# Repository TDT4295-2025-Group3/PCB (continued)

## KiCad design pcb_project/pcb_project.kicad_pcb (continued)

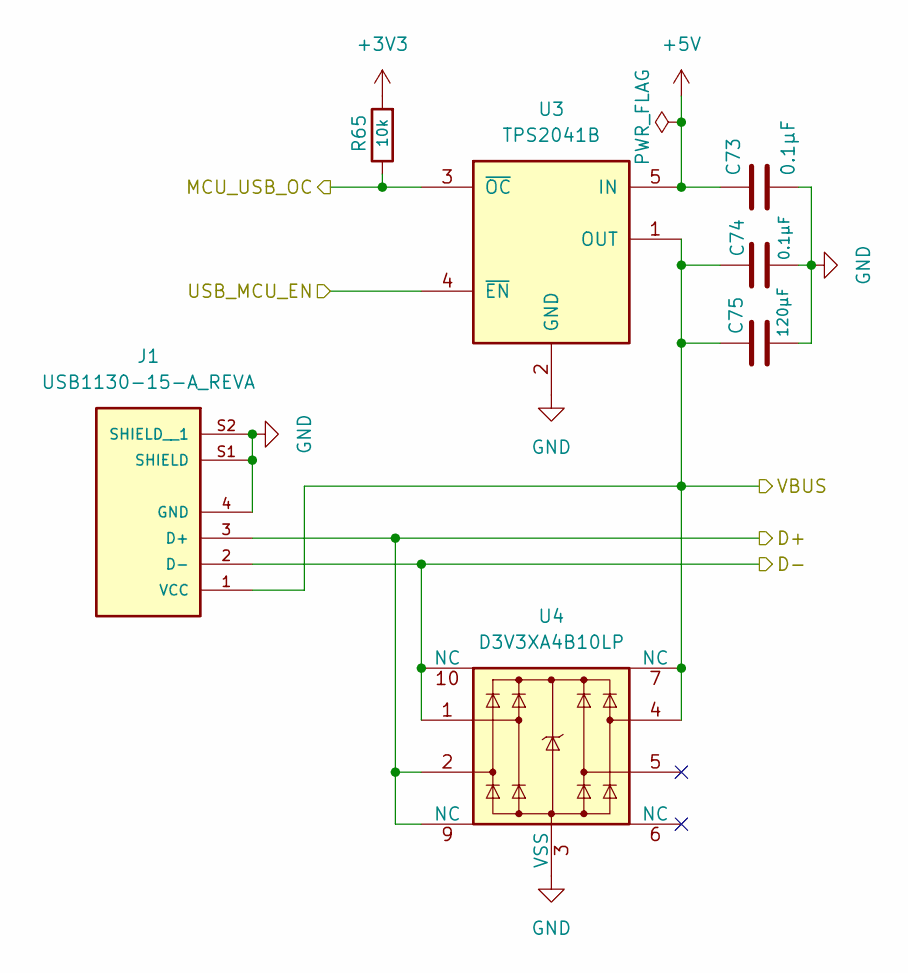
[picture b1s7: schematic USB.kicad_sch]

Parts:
C73: 0.1μF; C_0603_1608Metric_Pad1.08x0.95mm_HandSolder
C74: 0.1µF; C_0603_1608Metric_Pad1.08x0.95mm_HandSolder
C75: 120µF; CP_Elec_6.3x7.7
J1: USB1130-15-A_REVA; GCT_USB1130-15-A_REVA; PARTREV A
R65: 10k; R_0805_2012Metric_Pad1.20x1.40mm_HandSolder
U3: TPS2041B; SOT-23-5
U4: D3V3XA4B10LP; Diodes_UDFN-10_1.0x2.5mm_P0.5mm

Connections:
+3V3: R65.2; also elsewhere on the board
+5V: C73.1, U3.5 (IN); also elsewhere on the board
/MCU/OTG_HS_D+: J1.3 (D+), U4.2, U4.9 (NC); also elsewhere on the board
/MCU/OTG_HS_D-: J1.2 (D-), U4.1, U4.10 (NC); also elsewhere on the board
/MCU/PA9_OTG_HS_VBUS: C74.2, C75.2, J1.1 (VCC), U3.1 (OUT), U4.4, U4.7 (NC); also elsewhere on the board
/MCU/PB0_LPGPIO1_P9: R65.1, U3.3 (~OC); also elsewhere on the board
/MCU/PB1_LPGPIO1_P3: U3.4 (~EN); also elsewhere on the board
GND: C73.2, C74.1, C75.1, J1.4 (GND), J1.S1 (SHIELD), J1.S2 (SHIELD__1), U3.2 (GND), U4.3 (VSS), U4.8 (VSS); also elsewhere on the board

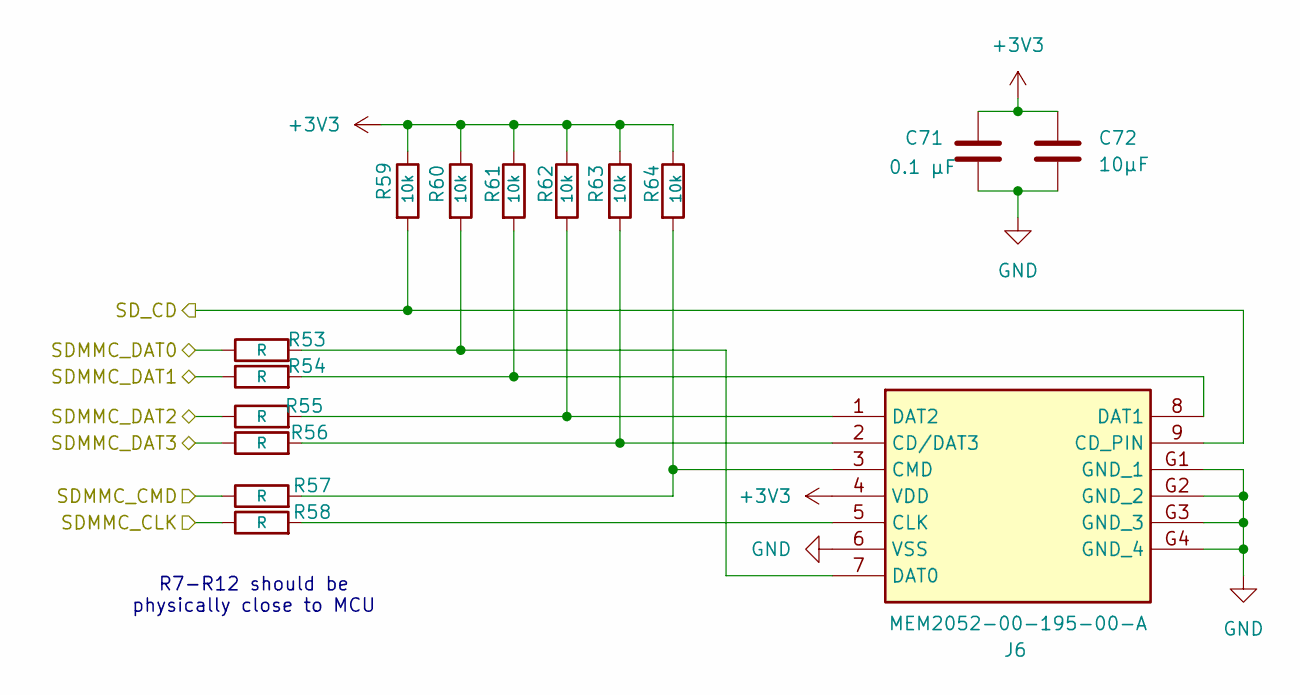
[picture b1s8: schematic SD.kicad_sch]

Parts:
C71: 0.1 µF; C_0603_1608Metric_Pad1.08x0.95mm_HandSolder
C72: 10µF; C_1206_3216Metric_Pad1.33x1.80mm_HandSolder
J6: MEM2052-00-195-00-A; MEM20520019500A; Mouser Part Number 640-MEM20520019500A
R53, R54, R55, R56, R57, R58: R; R_0805_2012Metric_Pad1.20x1.40mm_HandSolder
R59, R60, R61, R62, R63, R64: 10k; R_0805_2012Metric_Pad1.20x1.40mm_HandSolder

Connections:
+3V3: C71.1, C72.1, J6.4 (VDD), R59.1, R60.1, R61.1, R62.1, R63.1, R64.1; also elsewhere on the board
/MCU/PB4_LPGPIO1_P12: J6.9 (CD_PIN), R59.2; also elsewhere on the board
/MCU/PC8_SDMMC1_D0: R53.1; also elsewhere on the board
/MCU/PC9_SDMMC1_D1: R54.1; also elsewhere on the board
/MCU/PC10_SDMMC1_D2: R55.1; also elsewhere on the board
/MCU/PC11_SDMMC1_D3: R56.1; also elsewhere on the board
/MCU/PC12_SDMMC1_CK: R58.1; also elsewhere on the board
/MCU/PD2_SDMMC1_CMD: R57.1; also elsewhere on the board
GND: C71.2, C72.2, J6.6 (VSS), J6.G1 (GND_1), J6.G2 (GND_2), J6.G3 (GND_3), J6.G4 (GND_4); also elsewhere on the board
unnamed: J6.2 (CD/DAT3), R56.2, R63.2
unnamed: J6.5 (CLK), R58.2
unnamed: J6.3 (CMD), R57.2, R64.2
unnamed: J6.7 (DAT0), R53.2, R60.2
unnamed: J6.8 (DAT1), R54.2, R61.2
unnamed: J6.1 (DAT2), R55.2, R62.2

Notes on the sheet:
R7-R12 should be physically close to MCU

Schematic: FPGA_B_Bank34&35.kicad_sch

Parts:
C86: 47µF; C_1210_3225Metric_Pad1.33x2.70mm_HandSolder
C88: 1µF; C_0805_2012Metric_Pad1.18x1.45mm_HandSolder
C89: 0.01µF; C_0603_1608Metric_Pad1.08x0.95mm_HandSolder
C90, C91: 4.7µF; C_0603_1608Metric_Pad1.08x0.95mm_HandSolder
C92, C93, C94, C95: 0.47µF; C_0603_1608Metric_Pad1.08x0.95mm_HandSolder
J8: Conn_01x06_Pin; PinHeader_1x06_P2.54mm_Vertical
R66: 22k; R_0805_2012Metric_Pad1.20x1.40mm_HandSolder
R85, R86: 47; R_0805_2012Metric_Pad1.20x1.40mm_HandSolder
U1: XC7A100T-FTG256; Xilinx_FTG256
Y2: XLH736025.175000I; XLH730003580000I; Mouser Part Number 972-LH736025.175000I

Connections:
+3V3: C86.1, C88.1, C89.1, C90.1, C91.1, C92.1, C93.1, C94.1, C95.1, R66.1, U1.A6 (VCCO_35), U1.B3 (VCCO_35), U1.D7 (VCCO_35), U1.E4 (VCCO_35), U1.F1 (VCCO_35), U1.J2 (VCCO_35), Y2.1 (E/D_/_NC); also elsewhere on the board
/FPGA/B_Bank34&35/GPIO1: J8.1, U1.A7 (IO_L1N_T0_AD4N_35)
/FPGA/B_Bank34&35/GPIO2: J8.2, U1.B7 (IO_L1P_T0_AD4P_35)
/FPGA/B_Bank34&35/GPIO3: J8.3, U1.B6 (IO_L2P_T0_AD12P_35)
/FPGA/B_Bank34&35/GPIO4: J8.4, U1.B5 (IO_L2N_T0_AD12N_35)
/FPGA/B_Bank34&35/GPIO5: J8.5, U1.C7 (IO_L5P_T0_AD13P_35)
/FPGA/B_Bank34&35/GPIO6: J8.6, U1.C6 (IO_L5N_T0_AD13N_35)
/FPGA/HSYNC: R85.2; also elsewhere on the board
/FPGA/OSPI 0: U1.A2 (IO_L8N_T1_AD14N_35); also elsewhere on the board
/FPGA/OSPI 1: U1.A3 (IO_L4N_T0_35); also elsewhere on the board
/FPGA/OSPI 2: U1.A4 (IO_L3N_T0_DQS_AD5N_35); also elsewhere on the board
/FPGA/OSPI 3: U1.A5 (IO_L3P_T0_DQS_AD5P_35); also elsewhere on the board
/FPGA/OSPI 4: U1.E2 (IO_L10P_T1_AD15P_35); also elsewhere on the board
/FPGA/OSPI 5: U1.D1 (IO_L10N_T1_AD15N_35); also elsewhere on the board
/FPGA/OSPI 6: U1.C2 (IO_L7N_T1_AD6N_35); also elsewhere on the board
/FPGA/OSPI 7: U1.C1 (IO_L9P_T1_DQS_AD7P_35); also elsewhere on the board
/FPGA/OSPI CLK: U1.F5 (IO_L13P_T2_MRCC_35); also elsewhere on the board
/FPGA/OSPI CS: R66.2, U1.B2 (IO_L8P_T1_AD14P_35); also elsewhere on the board
/FPGA/VSYNC: R86.2; also elsewhere on the board
/VGA/B0: U1.E1 (IO_L15N_T2_DQS_35); also elsewhere on the board
/VGA/B1: U1.F3 (IO_L14N_T2_SRCC_35); also elsewhere on the board
/VGA/B2: U1.F2 (IO_L15P_T2_DQS_35); also elsewhere on the board
/VGA/B3: U1.G1 (IO_L17N_T2_35); also elsewhere on the board
/VGA/B4: U1.G5 (IO_L16P_T2_35); also elsewhere on the board
/VGA/G0: U1.J5 (IO_L19P_T3_35); also elsewhere on the board
/VGA/G1: U1.J1 (IO_L22N_T3_35); also elsewhere on the board
/VGA/G2: U1.H3 (IO_L21N_T3_DQS_35); also elsewhere on the board
/VGA/G3: U1.H2 (IO_L20P_T3_35); also elsewhere on the board
/VGA/G4: U1.H1 (IO_L20N_T3_35); also elsewhere on the board
/VGA/G5: U1.H5 (IO_L18P_T2_35); also elsewhere on the board
/VGA/R0: U1.L2 (IO_L23N_T3_35); also elsewhere on the board
/VGA/R1: U1.K3 (IO_L24P_T3_35); also elsewhere on the board
/VGA/R2: U1.K2 (IO_L24N_T3_35); also elsewhere on the board
/VGA/R3: U1.K1 (IO_L22P_T3_35); also elsewhere on the board
/VGA/R4: U1.J3 (IO_L21P_T3_DQS_35); also elsewhere on the board
GND: C86.2, C88.2, C89.2, C90.2, C91.2, C92.2, C93.2, C94.2, C95.2, U1.M3 (VCCO_34), U1.R4 (VCCO_34), U1.T1 (VCCO_34), Y2.3 (GND), Y2.6 (VDD); also elsewhere on the board
unnamed: R86.1, U1.K5 (IO_25_35)
unnamed: U1.D4 (IO_L12P_T1_MRCC_35), Y2.4 (OUT)
unnamed: R85.1, U1.L3 (IO_L23P_T3_35)

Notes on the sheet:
25.175Mhz
Vcco Bank 35, (Can share the 47µF) Add 2x4.7 and 4x0.47 per extra bank

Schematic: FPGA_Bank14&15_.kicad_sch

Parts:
C26: 47µF; C_1210_3225Metric_Pad1.33x2.70mm_HandSolder
C28, C30, C97, C98: 4.7µF; C_0603_1608Metric_Pad1.08x0.95mm_HandSolder
C31, C33, C34, C36, C99, C100, C101, C102: 0.47µF; C_0603_1608Metric_Pad1.08x0.95mm_HandSolder
C79 (2-3mm from SRAM Vdd)1, C85 (2-3mm from vdd)1, C103(2-3mmfromvdd)2, C106(2-3mmfromvdd)2: 0.1µF; C_0603_1608Metric_Pad1.08x0.95mm_HandSolder
C82, C104: 10µF; C_1206_3216Metric_Pad1.33x1.80mm_HandSolder
C83, C105: 1µF; C_0805_2012Metric_Pad1.18x1.45mm_HandSolder
C87: 100n; C_0603_1608Metric_Pad1.08x0.95mm_HandSolder
IC3, IC4: IS61WV204816BLL-10TLI; SOP50P2000X120-48N; Mouser Part Number 870-WV204816BLL10TLI
R67, R68, R69, R70, R71, R80, R81, R82, R83, R84: 47K; R_0805_2012Metric_Pad1.20x1.40mm_HandSolder
R76: 4.7k; R_0805_2012Metric_Pad1.20x1.40mm_HandSolder
R77: 4.7K; R_0805_2012Metric_Pad1.20x1.40mm_HandSolder
R78: 2.4k; R_0805_2012Metric_Pad1.20x1.40mm_HandSolder
U1: XC7A100T-FTG256; Xilinx_FTG256
U9: MT25QL128ABA1ESE-0SIT; SOP2_8PIN_208MIL_MRNFPGA_FLASH

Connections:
+3V3: C26.1, C28.1, C30.1, C31.1, C33.1, C34.1, C36.1, C79 (2-3mm from SRAM Vdd)1.1, C82.1, C83.1, C85 (2-3mm from vdd)1.1, C87.1, C97.1, C98.1, C99.1, C100.1, C101.1, C102.1, C103(2-3mmfromvdd)2.1, C104.1, C105.1, C106(2-3mmfromvdd)2.1, IC3.12 (VDD_1), IC3.36 (VDD_2), IC4.12 (VDD_1), IC4.36 (VDD_2), R67.1, R68.1, R69.1, R70.1, R71.1, R76.2, R77.1, R78.1, R80.1, R81.1, R82.1, R83.1, R84.1, U1.A16 (VCCO_15), U1.B13 (VCCO_15), U1.C10 (VCCO_15), U1.E14 (VCCO_15), U1.H15 (VCCO_15), U1.J12 (VCCO_15), U1.L16 (VCCO_14), U1.M13 (VCCO_14), U1.N10 (VCCO_14), U1.P7 (VCCO_14), U1.R14 (VCCO_14), U1.T11 (VCCO_14), U9.8 (VCC); also elsewhere on the board
/FPGA/A_Bank14&15/A0: IC4.5 (A0), U1.T14 (IO_L10P_T1_D14_14)
/FPGA/A_Bank14&15/A0IC3: IC3.5 (A0), U1.A13 (IO_L7P_T1_AD2P_15)
/FPGA/A_Bank14&15/A1: IC4.4 (A1), U1.P13 (IO_L11N_T1_SRCC_14)
/FPGA/A_Bank14&15/A1IC3: IC3.4 (A1), U1.E12 (IO_L13P_T2_MRCC_15)
/FPGA/A_Bank14&15/A2: IC4.3 (A2), U1.R13 (IO_L16P_T2_CSI_B_14)
/FPGA/A_Bank14&15/A2IC3: IC3.3 (A2), U1.C14 (IO_L8P_T1_AD10P_15)
/FPGA/A_Bank14&15/A3: IC4.2 (A3), U1.T13 (IO_L16N_T2_A15_D31_14)
/FPGA/A_Bank14&15/A3IC3: IC3.2 (A3), U1.A14 (IO_L7N_T1_AD2N_15)
/FPGA/A_Bank14&15/A4: IC4.1 (A4), U1.N12 (IO_L13N_T2_MRCC_14)
/FPGA/A_Bank14&15/A4IC3: IC3.1 (A4), U1.B14 (IO_L8N_T1_AD10N_15)
/FPGA/A_Bank14&15/A5: IC4.48 (A5), U1.R12 (IO_L15P_T2_DQS_RDWR_B_14)
/FPGA/A_Bank14&15/A5IC3: IC3.48 (A5), U1.D14 (IO_L15P_T2_DQS_15)
/FPGA/A_Bank14&15/A6: IC4.47 (A6), U1.T12 (IO_L15N_T2_DQS_DOUT_CSO_B_14)
/FPGA/A_Bank14&15/A6IC3: IC3.47 (A6), U1.A15 (IO_L9N_T1_DQS_AD3N_15)
/FPGA/A_Bank14&15/A7: IC4.46 (A7), U1.P11 (IO_L14N_T2_SRCC_14)
/FPGA/A_Bank14&15/A7IC3: IC3.46 (A7), U1.B15 (IO_L9P_T1_DQS_AD3P_15)
/FPGA/A_Bank14&15/A8: IC4.45 (A8), U1.R11 (IO_L17N_T2_A13_D29_14)
/FPGA/A_Bank14&15/A8IC3: IC3.45 (A8), U1.E13 (IO_L13N_T2_MRCC_15)
/FPGA/A_Bank14&15/A9: IC4.30 (A9), U1.M6 (IO_L19P_T3_A10_D26_14)
/FPGA/A_Bank14&15/A9IC3: IC3.30 (A9), U1.H12 (IO_L20P_T3_A20_15)
/FPGA/A_Bank14&15/A10: IC4.29 (A10), U1.R6 (IO_L24P_T3_A01_D17_14)
/FPGA/A_Bank14&15/A10IC3: IC3.29 (A10), U1.H16 (IO_L22P_T3_A17_15)
/FPGA/A_Bank14&15/A11: IC4.28 (A11), U1.P6 (IO_25_14)
/FPGA/A_Bank14&15/A11IC3: IC3.28 (A11), U1.H14 (IO_L24P_T3_RS1_15)
/FPGA/A_Bank14&15/A12: IC4.27 (A12), U1.T5 (IO_L23N_T3_A02_D18_14)
/FPGA/A_Bank14&15/A12IC3: IC3.27 (A12), U1.H13 (IO_L20N_T3_A19_15)
/FPGA/A_Bank14&15/A13: IC4.26 (A13), U1.R5 (IO_L23P_T3_A03_D19_14)
/FPGA/A_Bank14&15/A13IC3: IC3.26 (A13), U1.J16 (IO_L23N_T3_FWE_B_15)
/FPGA/A_Bank14&15/A14: IC4.25 (A14), U1.N6 (IO_L19N_T3_A09_D25_VREF_14)
/FPGA/A_Bank14&15/A14IC3: IC3.25 (A14), U1.J15 (IO_L23P_T3_FOE_B_15)
/FPGA/A_Bank14&15/A15: IC4.24 (A15), U1.K12 (IO_0_14)
/FPGA/A_Bank14&15/A15IC3: IC3.24 (A15), U1.C8 (IO_L1P_T0_AD0P_15)
/FPGA/A_Bank14&15/A16: IC4.23 (A16), U1.L14 (IO_L4P_T0_D04_14)
/FPGA/A_Bank14&15/A16IC3: IC3.23 (A16), U1.A8 (IO_L2P_T0_AD8P_15)
/FPGA/A_Bank14&15/A17: IC4.22 (A17), U1.M16 (IO_L7P_T1_D09_14)
/FPGA/A_Bank14&15/A17IC3: IC3.22 (A17), U1.D8 (IO_L6P_T0_15)
/FPGA/A_Bank14&15/A18: IC4.21 (A18), U1.L13 (IO_L5N_T0_D07_14)
/FPGA/A_Bank14&15/A18IC3: IC3.21 (A18), U1.D9 (IO_L6N_T0_VREF_15)
/FPGA/A_Bank14&15/A19: IC4.20 (A19), U1.M14 (IO_L4N_T0_D05_14)
/FPGA/A_Bank14&15/A19IC3: IC3.20 (A19), U1.A9 (IO_L2N_T0_AD8N_15)
/FPGA/A_Bank14&15/A20: IC4.31 (A20), U1.R7 (IO_L24N_T3_A00_D16_14)
/FPGA/A_Bank14&15/A20IC3: IC3.31 (A20), U1.G12 (IO_L19N_T3_A21_VREF_15)
/FPGA/A_Bank14&15/CLK side: U9.6 (C); also elsewhere on the board
/FPGA/A_Bank14&15/CSIC3: IC3.7 (CS#), R81.2, U1.D11 (IO_L14N_T2_SRCC_15)
/FPGA/A_Bank14&15/CSIC4: IC4.7 (CS#), R70.2, U1.T15 (IO_L10N_T1_D15_14)
/FPGA/A_Bank14&15/D02: R77.2, U1.K15 (IO_L2P_T0_D02_14), U9.3 (W#/DQ2)
/FPGA/A_Bank14&15/D03: R76.1, U1.K16 (IO_L2N_T0_D03_14), U9.7 (DQ3/HOLD#)
/FPGA/A_Bank14&15/DIN: U1.J14 (IO_L1N_T0_D01_DIN_14), U9.2 (DQ1)
/FPGA/A_Bank14&15/FCS_B: R78.2, U1.L12 (IO_L6P_T0_FCS_B_14), U9.1 (S#)
/FPGA/A_Bank14&15/IO00: IC4.8 (I/O0), U1.N13 (IO_L11P_T1_SRCC_14)
/FPGA/A_Bank14&15/IO00IC3: IC3.8 (I/O0), U1.B12 (IO_L5P_T0_AD9P_15)
/FPGA/A_Bank14&15/IO01: IC4.9 (I/O1), U1.R15 (IO_L9P_T1_DQS_14)
/FPGA/A_Bank14&15/IO01IC3: IC3.9 (I/O1), U1.A12 (IO_L5N_T0_AD9N_15)
/FPGA/A_Bank14&15/IO02: IC4.10 (I/O2), U1.R16 (IO_L9N_T1_DQS_D13_14)
/FPGA/A_Bank14&15/IO02IC3: IC3.10 (I/O2), U1.C11 (IO_L11P_T1_SRCC_15)
/FPGA/A_Bank14&15/IO03: IC4.11 (I/O3), U1.P14 (IO_L12N_T1_MRCC_14)
/FPGA/A_Bank14&15/IO03IC3: IC3.11 (I/O3), U1.B11 (IO_L4N_T0_15)
/FPGA/A_Bank14&15/IO04: IC4.14 (I/O4), U1.P15 (IO_L8P_T1_D11_14)
/FPGA/A_Bank14&15/IO04IC3: IC3.14 (I/O4), U1.E11 (IO_L14P_T2_SRCC_15)
/FPGA/A_Bank14&15/IO05: IC4.15 (I/O5), U1.P16 (IO_L8N_T1_D12_14)
/FPGA/A_Bank14&15/IO05IC3: IC3.15 (I/O5), U1.B10 (IO_L4P_T0_15)
/FPGA/A_Bank14&15/IO06: IC4.16 (I/O6), U1.N14 (IO_L12P_T1_MRCC_14)
/FPGA/A_Bank14&15/IO06IC3: IC3.16 (I/O6), U1.A10 (IO_L3N_T0_DQS_AD1N_15)
/FPGA/A_Bank14&15/IO07: IC4.17 (I/O7), U1.M12 (IO_L6N_T0_D08_VREF_14)
/FPGA/A_Bank14&15/IO07IC3: IC3.17 (I/O7), U1.C9 (IO_L1N_T0_AD0N_15)
/FPGA/A_Bank14&15/IO08: IC4.32 (I/O8), U1.T7 (IO_L21P_T3_DQS_14)
/FPGA/A_Bank14&15/IO8IC3: IC3.32 (I/O8), U1.G16 (IO_L22N_T3_A16_15)
/FPGA/A_Bank14&15/IO09: IC4.33 (I/O9), U1.P8 (IO_L20P_T3_A08_D24_14)
/FPGA/A_Bank14&15/IO9IC3: IC3.33 (I/O9), U1.G14 (IO_L21P_T3_DQS_15)
/FPGA/A_Bank14&15/IO10: IC4.34 (I/O10), U1.R8 (IO_L20N_T3_A07_D23_14)
/FPGA/A_Bank14&15/IO10IC3: IC3.34 (I/O10), U1.F14 (IO_L21N_T3_DQS_A18_15)
/FPGA/A_Bank14&15/IO11: IC4.35 (I/O11), U1.T8 (IO_L21N_T3_DQS_A06_D22_14)
/FPGA/A_Bank14&15/IO11IC3: IC3.35 (I/O11), U1.F15 (IO_L18P_T2_A24_15)
/FPGA/A_Bank14&15/IO12: IC4.38 (I/O12), U1.N9 (IO_L18P_T2_A12_D28_14)
/FPGA/A_Bank14&15/IO12IC3: IC3.38 (I/O12), U1.F13 (IO_L16N_T2_A27_15)
/FPGA/A_Bank14&15/IO13: IC4.39 (I/O13), U1.P9 (IO_L18N_T2_A11_D27_14)
/FPGA/A_Bank14&15/IO13IC3: IC3.39 (I/O13), U1.E16 (IO_L17P_T2_A26_15)
/FPGA/A_Bank14&15/IO14: IC4.40 (I/O14), U1.T9 (IO_L22P_T3_A05_D21_14)
/FPGA/A_Bank14&15/IO14IC3: IC3.40 (I/O14), U1.F12 (IO_L16P_T2_A28_15)
/FPGA/A_Bank14&15/IO15: IC4.41 (I/O15), U1.P10 (IO_L14P_T2_SRCC_14)
/FPGA/A_Bank14&15/IO15IC3: IC3.41 (I/O15), U1.D16 (IO_L17N_T2_A25_15)
/FPGA/A_Bank14&15/LBIC3: IC3.42 (LB#), R84.2, U1.D15 (IO_L15N_T2_DQS_ADV_B_15)
/FPGA/A_Bank14&15/LBIC4: IC4.42 (LB#), R68.2, U1.R10 (IO_L17P_T2_A14_D30_14)
/FPGA/A_Bank14&15/MOSI: U1.J13 (IO_L1P_T0_D00_MOSI_14), U9.5 (DQ0)
/FPGA/A_Bank14&15/OEIC3: IC3.44 (OE#), R82.2, U1.B16 (IO_L10N_T1_AD11N_15)
/FPGA/A_Bank14&15/OEIC4: IC4.44 (OE#), R67.2, U1.N11 (IO_L13P_T2_MRCC_14)
/FPGA/A_Bank14&15/UBIC3: IC3.43 (UB#), R83.2, U1.C16 (IO_L10P_T1_AD11P_15)
/FPGA/A_Bank14&15/UBIC4: IC4.43 (UB#), R69.2, U1.T10 (IO_L22N_T3_A04_D20_14)
/FPGA/A_Bank14&15/WEIC3: IC3.18 (WE#), R80.2, U1.B9 (IO_L3P_T0_DQS_AD1P_15)
/FPGA/A_Bank14&15/WEIC4: IC4.18 (WE#), R71.2, U1.N16 (IO_L7N_T1_D10_14)
GND: C26.2, C28.2, C30.2, C31.2, C33.2, C34.2, C36.2, C79 (2-3mm from SRAM Vdd)1.2, C82.2, C83.2, C85 (2-3mm from vdd)1.2, C87.2, C97.2, C98.2, C99.2, C100.2, C101.2, C102.2, C103(2-3mmfromvdd)2.2, C104.2, C105.2, C106(2-3mmfromvdd)2.2, IC3.13 (VSS_1), IC3.37 (VSS_2), IC4.13 (VSS_1), IC4.37 (VSS_2), U9.4 (VSS); also elsewhere on the board

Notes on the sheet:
SRAM Decoupling (IC3)
For Vcco Bank x, (Can share the 47µF) Add 2x4.7 and 4x0.47 per extra bank
Vcco Bank 14,15
SRAM Decoupling (IC4)

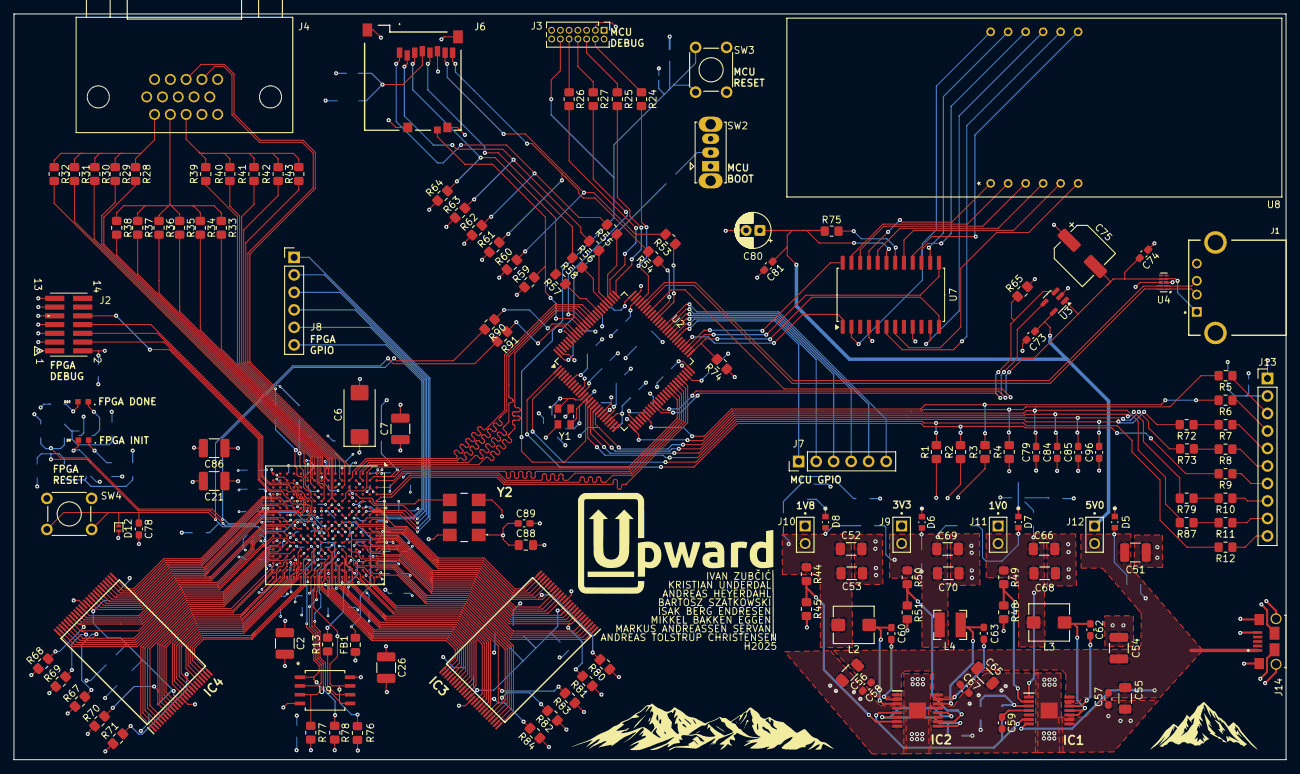
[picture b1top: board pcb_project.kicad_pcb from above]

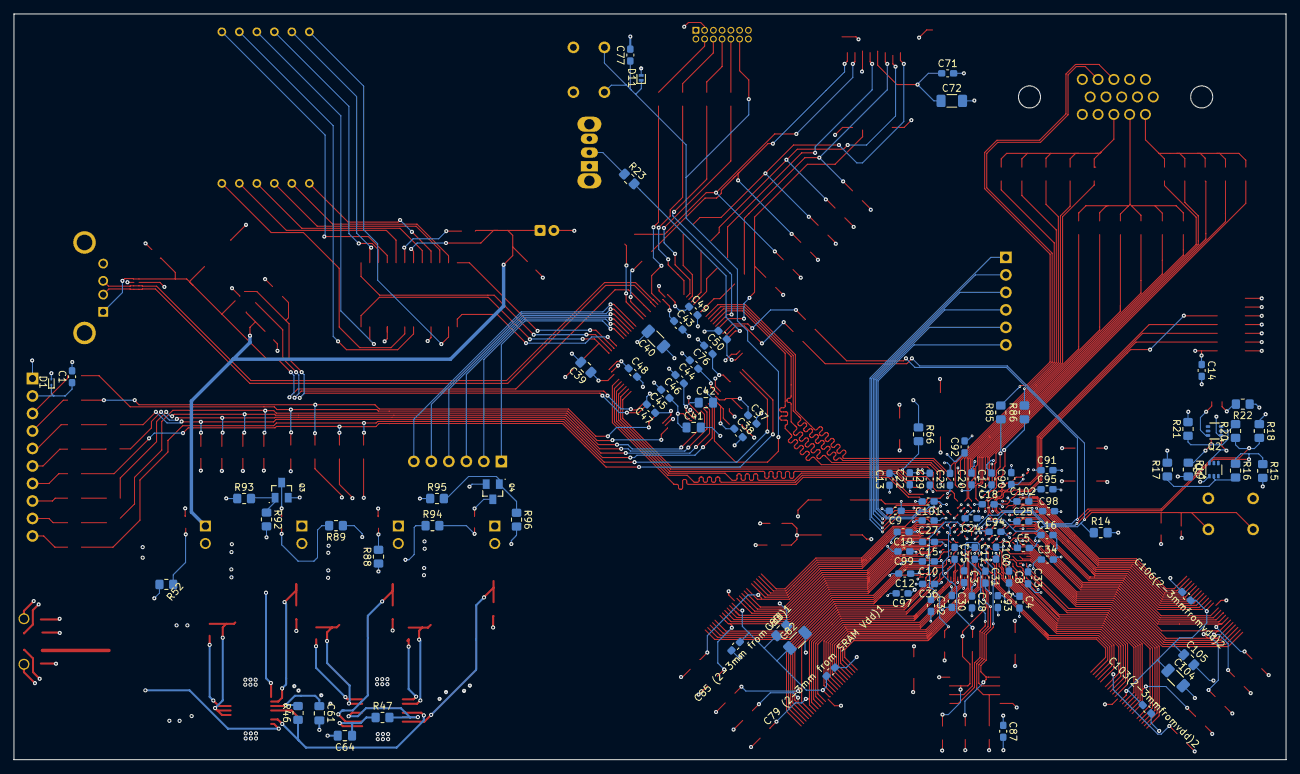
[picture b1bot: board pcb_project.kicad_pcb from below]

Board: 4 copper layers, 184.6 x 108.2 mm, 250 parts (101 on the bottom side), 253 nets.

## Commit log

2025-09-12 Initial project structure
2025-09-12 Add SD,VGA,Power modules
2025-09-12 Create lib structure and add MEM2052
2025-09-12 Create MicroSD circuit
2025-09-12 Add VGA with 4bit DAC
2025-09-12 Create power supply circuit
2025-09-15 Add USB (have questions)
2025-09-17 Controller joystick setup
2025-09-17 Actuall controller joystick schematic
2025-09-17 Add symbolforLED
2025-09-17 Add button symbol
2025-09-17 Finish controller schema
2025-09-17 Initial MCU schematic
2025-09-17 LED & FPGA_Started
2025-09-19 Add decoupling capacitors for FPGA
2025-09-19 Update FPGA pin ids
2025-09-19 Add switch for MCU BOOT pin
2025-09-19 Sync sheet pins
2025-09-19 Add ESB protection to MicroSd reader
2025-09-19 Add labels for MCU pins
2025-09-19 Add MicroUSB as power input
2025-09-19 Update USB circuits
2025-09-19 Crystal + SPI flash FPGA
2025-09-21 Connect Controller, LED-display, USB and SD reader to MCU
2025-09-21 Add framebuffer SRAM
2025-09-21 Setup pins for OCTOSPI
2025-09-21 Add FPGA JTAG
2025-09-21 Clean up MCU pin labels
2025-09-22 16bit binary weighted dac, FPGA power
2025-09-22 Add pin placement for OSPI on FPGA, not wired in root yet
2025-09-22 Update USB component and redo pin choices for MCU
2025-09-22 SPI connection root
2025-09-22 VGA Root + Change FPGA Oscilator to 3.3v
2025-09-22 Fix flash memory clk wiring
2025-09-22 Add FPGA configuration LED's, config pins, no connect symbols
2025-09-22 Remove unused inputs to FPGA in root
2025-09-23 ERC fixes, some remain
2025-09-23 Fix USB pins and other ERC errors
2025-09-23 ERC done
2025-09-24 Fix JTAG connector, add pullups (FPGA has internal pullups as well), add some capacitor footprints
2025-09-24 Add FPGA DONE AND PROGRAM_B (reset) to MCU GPIO
2025-09-24 Tied unused FGPA vcco to ground. Moved decoupling to all banks.
2025-09-24 Add symbol&footprint for I2C 5v->3.3V level shifting. Only implement VGA info -> MCU if we have time
2025-09-24 Forgot CTRL +S lol
2025-09-24 Add most footprints, missing some inductors and 3 buttons
2025-09-24 Basic layout, still missing some footprints
2025-09-25 Move controller to its own project
2025-09-25 Fix Program_B that was at wrong wire
2025-09-25 Add debouncing capasitor for MCU reset button
2025-09-25 Add debounce cap on FPGA reset, add second sram symbol
2025-09-25 Update power connectors
2025-09-25 FPGA decoupler
2025-09-25 Initial MicroSD reader layout
2025-09-26 Fix more footprints and add MicroSD reader 3D model
2025-09-26 Add footprints for switches
2025-09-26 Add another SRAM
2025-09-26 Fix rest of footprints
2025-09-26 Fix ERC errors and update PCB from schematic
2025-09-26 Initial components positioning
2025-09-26 Initial FPGA ballout and vga
2025-09-27 FPGA Dog Bone wires
2025-09-27 Minor schematic changes for easier Layout
    - Proper TVS symbol for MicroSD
    - Rename USB data lines net name to allow for differential routing
    - Change SDMMC_CD GPIO to easier MCU pin
2025-09-27 MicroSD layout, TVS issues
2025-09-27 Layout MCU debug connector, reset and boot buttons
2025-09-27 Led display layout
2025-09-27 Update controller connector schematic
    - Fix pin component so it works in layout
    - Move RC filters from controller to PCB
    - Remove pullups from controller as they are on pcb
2025-09-27 Initial USB Layout, wrong USB footprint
2025-09-27 Custom controller layout and some pin changes
2025-09-27 Routed out SPI from FPGA
2025-09-28 Layout OSPI from MCU
2025-09-28 Change FPGA OSPI pins and connect to MCU only top layer
2025-09-28 Layout with proper USB component
2025-09-28 Clean up routing around MCU and ish length match OSPI
2025-09-28 Power supply layout
2025-09-28 More length matching OSPI
2025-09-29 More fpga outwires
2025-09-29 More FPGA ballout
2025-09-29 Set PCB size
2025-09-29 Done and Init B led circuitry
2025-09-29 VGA Layout in copy
2025-09-29 Move VGA Layout from copy to actual board
2025-09-29 All IC3 outs
2025-09-29 SRAM1 wiring unconnected
2025-09-29 Fix IC3 wires
2025-09-29 Fix IC3 connections in schematic, F12-A6 and E12 - A5, are unconnected and needs to be fixed on the fpga balls
2025-09-29 Route SRAM 2 unconnected
2025-09-29 IC4 schematic wiring. MISSING UN AND LB!
2025-09-29 Finish SRAM1 Layout
2025-09-29 Fix IC4 missing FPGA pinouts with new labels
2025-09-29 Finish SRAM2 Layout
2025-09-29 Move div layout to use space better and some clean up
2025-09-29 Fix OSPI line and MCU capasitors
2025-09-29 Clean up FPGA pins, and other small improvements
2025-09-30 FLASH Pcb layout
2025-09-30 FPGA power and grround own vias
2025-09-30 Fix power supply layout
2025-09-30 Add a few decouplers under FPGA. Lots starting to look like swiss cheese under here
2025-09-30 Fill ground and pwr layers and connect pins to them
2025-09-30 Finish FPGA leds, button and debug
2025-09-30 Finish a bit more open connections
2025-09-30 Add logo
2025-09-30 Add VGA 3D model
2025-09-30 Small fixes and gather all remaining capasitors
2025-09-30 Update slikscreen
2025-09-30 Add mountains
2025-09-30 Changed resistor values for H/VSYNC to 47
2025-10-01 Set net class that allows for 2x wires between FPGA balls
2025-10-01 Placed and routed most decouplers, and the center of FPGA power/gnd pins, this lives on hopes and dreams
2025-10-02 Working out from the center of FPGA. Hopes and dreams gambit accepted
2025-10-02 Update PSU layout with proper thermal zones
2025-10-02 Update zone min_clearance
2025-10-02 Add year to silkscreen
2025-10-02 Add GPIO pins for MCU and FPGA
2025-10-02 Changed capacitor sizes. Now it's even more difficult
2025-10-02 Update logo (previous changes dissapeared)
2025-10-02 Fix PSU
2025-10-02 Add GPIO pins to layout
2025-10-02 Reroute USB D+/D- with correct trace width
2025-10-02 FPGA capacitors and wire out SRAM pins
2025-10-03 Left SRAM no vias
2025-10-03 Right SRAM no vias
2025-10-03 Fix remaining FPGA capasitors
2025-10-04 Connected wires for SRAMs
2025-10-04 Move and reconnect FPGA Debug/LED/Button
2025-10-04 Finish SRAM layout
2025-10-04 Reconnect VGA and FPGA
2025-10-04 Add pwr LEDS, fix FPGA led tranistor values
2025-10-04 Reconnect FPGA GPIO
2025-10-04 Add new LED curcuits to layout
2025-10-05 Rename FPGA labels such that there are no duplicates.
2025-10-05 LED PWR PCB circuit. Watch the head of the ship!
2025-10-05 Moved 5v transistor to line up with the helm of the ship
2025-10-05 FPGA flash, all SIG_MID wires removed
2025-10-05 Some clean up
2025-10-05 First attempt at routing 1V0&1V8 on PWR layer
2025-10-05 DRC; Remaining: Layer Priorities, ESD's, SD card ESD thingy, Silksreen
2025-10-05 Fix DRC errors
    - Remove ESD as they do not work
    - Increase zone priotity for overlapping zones
    - Connect some unconnected pads
2025-10-05 Remove Power esd diode
2025-10-05 Fix edge cuts
2025-10-05 Update net on unconnected pin
2025-10-05 Update silkscreen
2025-10-05 Length match OSPI +/-0.0666...mm
2025-10-05 Go from 6 to 4 layers
2025-10-08 Add Micro USB footprints
2025-10-08 Increase via hole size to 0.15mm
2025-10-08 Update MicroUSB symbol and edit footprint to match constraints
2025-10-08 Change NET on unconnected pin to 3V3
